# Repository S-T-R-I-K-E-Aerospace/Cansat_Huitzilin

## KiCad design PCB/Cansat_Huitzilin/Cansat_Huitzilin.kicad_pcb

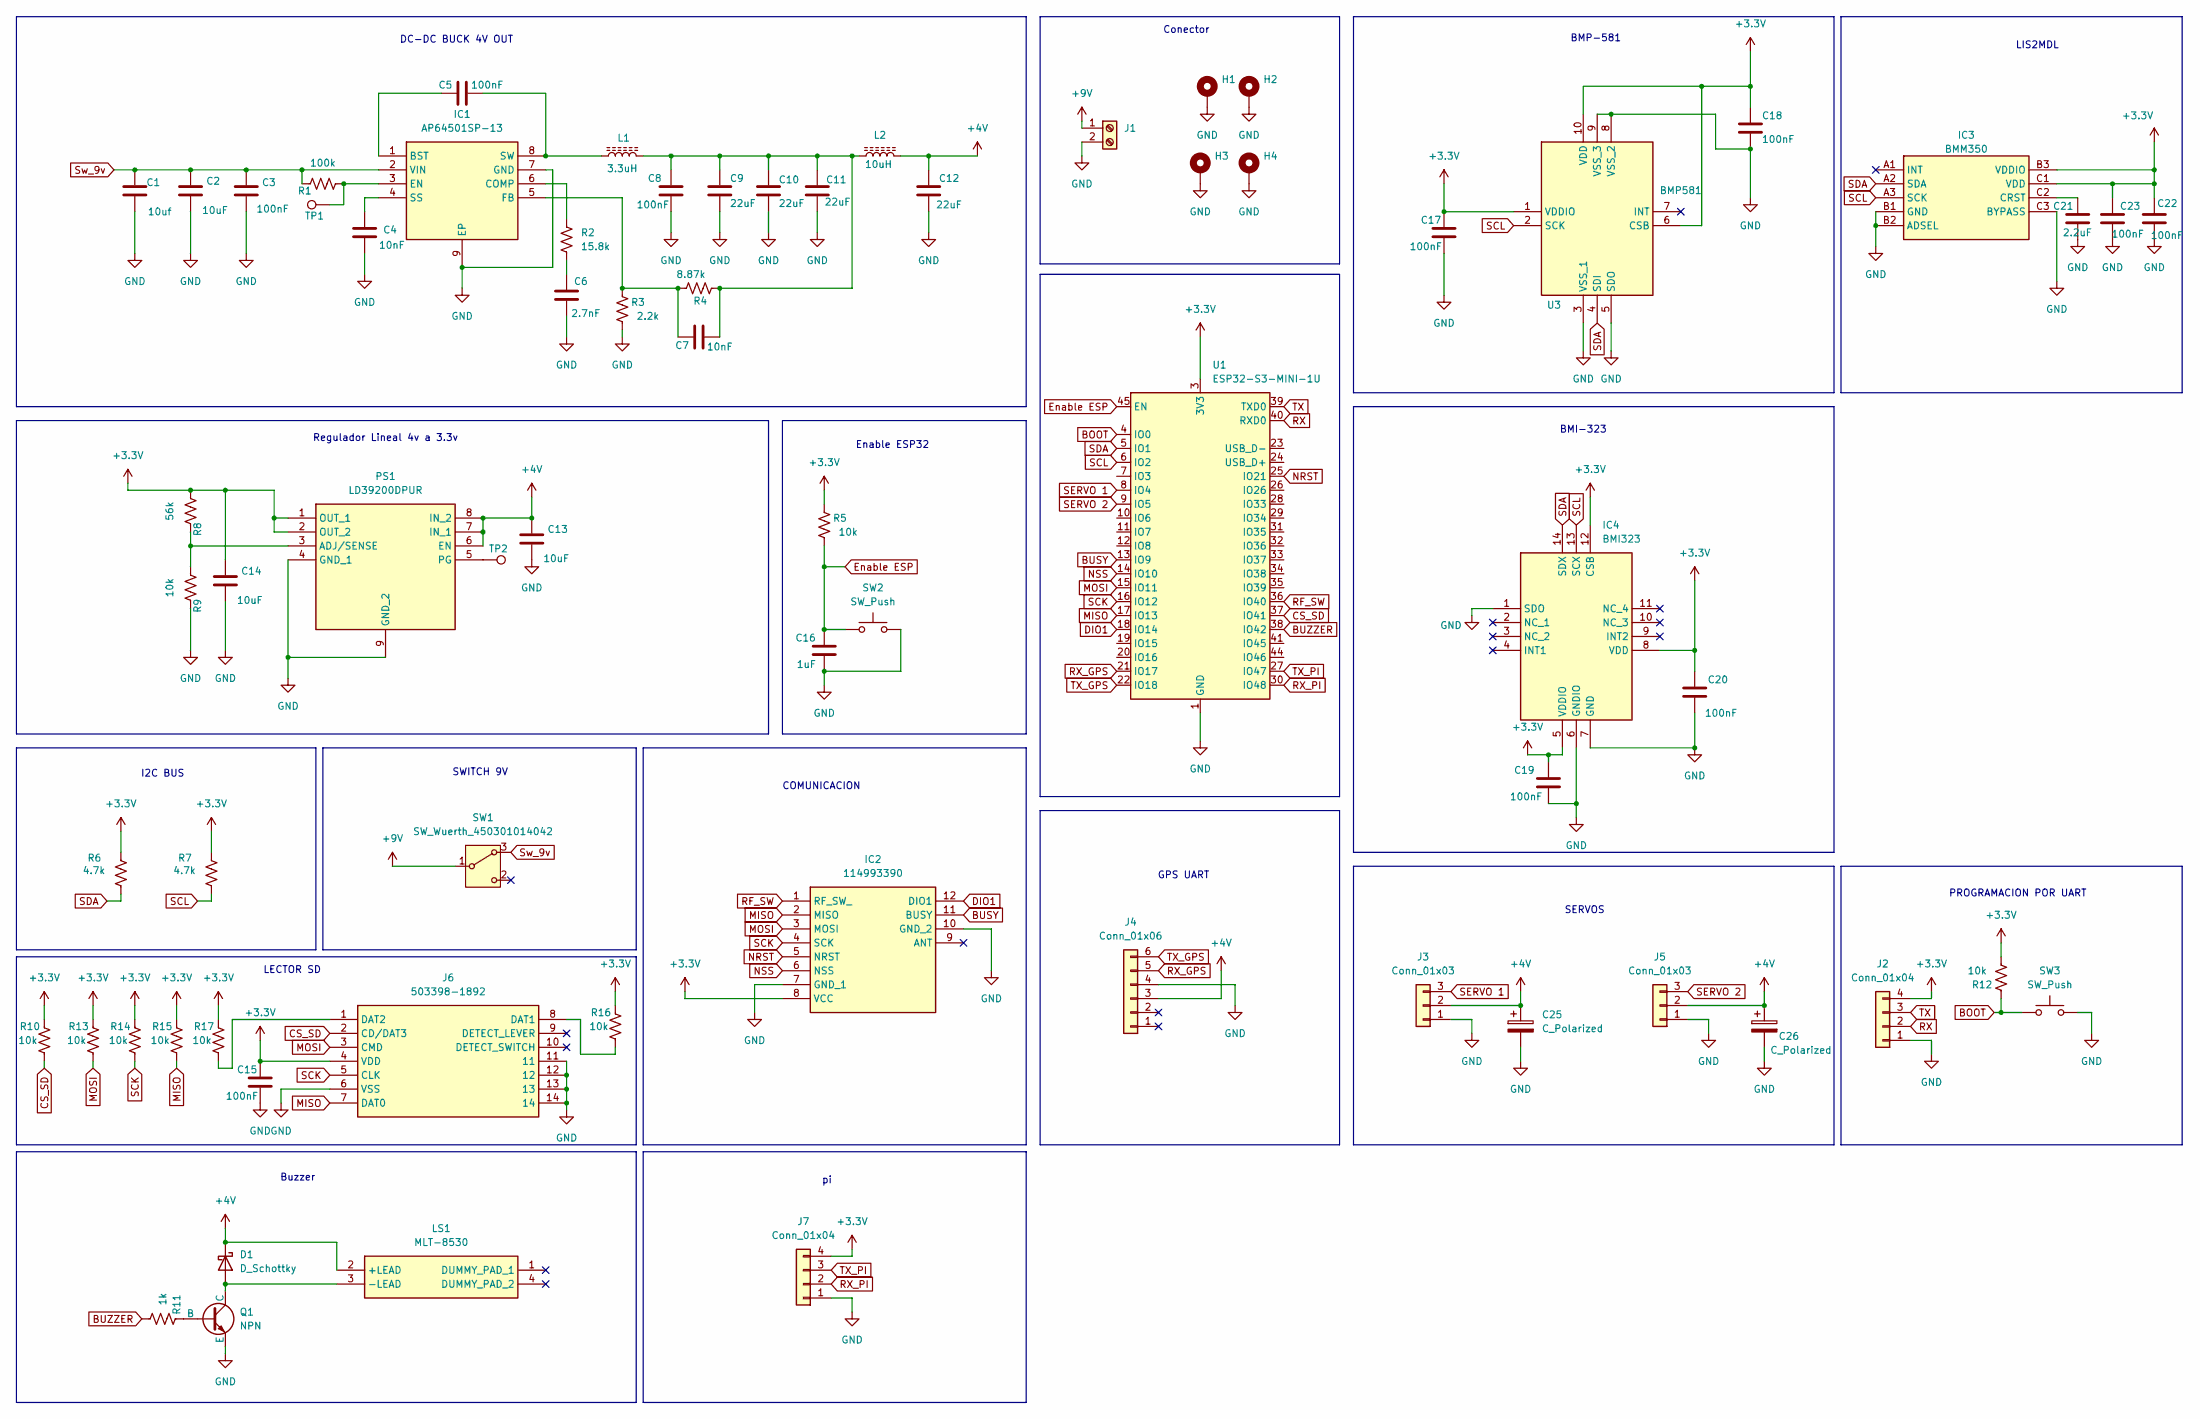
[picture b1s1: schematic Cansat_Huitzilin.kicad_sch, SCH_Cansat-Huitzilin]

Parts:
C1: 10uf; C_0603_1608Metric; Part Number CL10A106MA8NRNC
C2, C13, C14: 10uF; C_0603_1608Metric; Part Number CL10A106MA8NRNC
C3, C5, C8, C15, C17, C18, C19, C20, C22, C23: 100nF; C_0603_1608Metric; Part Number E0603X7R104K500NTD
C4, C7: 10nF; C_0603_1608Metric; Part Number C0201X7R103K500NTA
C6: 2.7nF; C_0603_1608Metric; Part Number C0603C272K5RACTU
C9, C10, C11, C12: 22uF; C_0603_1608Metric
C16: 1uF; C_0603_1608Metric; Part Number CL31B105KBHNNNE
C21: 2.2uF; C_0603_1608Metric; Part Number CL10E224KA84PNC
C25, C26: C_Polarized; CP_Elec_6.3x5.8; Part Number UUD1E101MCL1GS
D1: D_Schottky; D_SOD-123F; Part Number DSS14U
H1, H2, H3, H4: MountingHole_Pad; MountingHole_3.2mm_M3_Pad_Via
IC1: AP64501SP-13; SOIC-8-1EP_3.9x4.9mm_P1.27mm_EP2.29x3mm; Manufacturer_Part_Number AP64501SP-13; Mouser Part Number 621-AP64501SP-13
IC2: 114993390; Mouser Part Number 713-114993390
IC3: BMM350; BGA9C40P3X3_128X128X54; Manufacturer_Part_Number BMM350; Mouser Part Number 262-BMM350
IC4: BMI323; Manufacturer_Part_Number BMI323; Mouser Part Number 262-BMI323
J1: Screw_Terminal_01x02; TerminalBlock_MaiXu_MX126-5.0-02P_1x02_P5.00mm
J2, J7: Conn_01x04; PinHeader_1x04_P2.54mm_Vertical
J3, J5: Conn_01x03; PinHeader_1x03_P2.54mm_Vertical
J4: Conn_01x06; SM06BPASSTBTLFSN
J6: 503398-1892; 5033981892; Manufacturer_Part_Number 503398-1892; Mouser Part Number 538-503398-1892
L1: 3.3uH; L_Wuerth_WE-PD-Typ-LS; Part Number 7447779003
L2: 10uH; L_1210_3225Metric_Pad1.42x2.65mm_HandSolder
LS1: MLT-8530; MLT8530; Manufacturer_Part_Number MLT-8530
PS1: LD39200DPUR; SON80P400X400X100-9N-D; Mouser Part Number 511-LD39200DPUR
Q1: NPN; SOT-23; Part Number S8050
R1: 100k; R_0603_1608Metric; Part Number RC0805FR-07100KL
R2: 15.8k; R_0603_1608Metric; Part Number RMCF0805FT15K8
R3: 2.2k; R_0603_1608Metric; Part Number CRG0805F2K2
R4: 8.87k; R_0603_1608Metric; Part Number RC0805FR-078K87L
R5, R10, R12, R13, R14, R15, R16, R17: 10k; R_0603_1608Metric; Part Number CRCW080510K0FKEA
R6, R7: 4.7k; R_0603_1608Metric; Part Number CRCW08054K70FKEAC
R8: 56k; R_0603_1608Metric; Part Number RC0805FR-07100KL
R9: 10k; R_0603_1608Metric; Part Number RC0805FR-07100KL
R11: 1k; R_0603_1608Metric; Part Number CRCW080510K0FKEA
SW1: SW_Wuerth_450301014042; SW_Slide-03_Wuerth-WS-SLTV_10x2.5x6.4_P2.54mm
SW2, SW3: SW_Push; SW_SPST_SKQG_WithoutStem
TP1, TP2: TestPoint; TestPoint_Pad_D1.0mm
U1: ESP32-S3-MINI-1U; ESP32-S2-MINI-1U
U3: BMP581; Manufacturer_Part_Number BMP581; Mouser Part Number 262-BMP581

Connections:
+3.3V: C14.1, C15.1, C17.1, C18.1, C19.1, C20.1, C22.2, C23.1, IC2.8 (VCC), IC3.B3 (VDDIO), IC3.C1 (VDD), IC4.5 (VDDIO), IC4.8 (VDD), IC4.12 (CSB), J2.4, J6.4 (VDD), J7.4, PS1.1 (OUT_1), PS1.2 (OUT_2), R5.2, R6.1, R7.1, R8.2, R10.2, R12.1, R13.2, R14.2, R15.2, R16.2, R17.2, U1.3 (3V3), U3.1 (VDDIO), U3.6 (CSB), U3.10 (VDD)
+4V: C12.1, C13.1, C25.1, C26.1, D1.1 (K), J3.2, J4.3, J5.2, L2.2, LS1.2 (+LEAD), PS1.6 (EN), PS1.7 (IN_1), PS1.8 (IN_2)
+9V: J1.1, SW1.1 (B)
BOOT: R12.2, SW3.1, U1.4 (IO0)
BUSY: IC2.11 (BUSY), U1.13 (IO9)
BUZZER: R11.1, U1.38 (IO42)
CS_SD: J6.2 (CD/DAT3), R10.1, U1.37 (IO41)
DIO1: IC2.12 (DIO1), U1.18 (IO14)
Enable ESP: C16.1, R5.1, SW2.1, U1.45 (EN)
GND: C1.2, C2.2, C3.2, C4.2, C6.2, C8.2, C9.2, C10.2, C11.2, C12.2, C13.2, C14.2, C15.2, C16.2, C17.2, C18.2, C19.2, C20.2, C21.2, C22.1, C23.2, C25.2, C26.2, H1.1, H2.1, H3.1, H4.1, IC1.7 (GND), IC1.9 (EP), IC2.7 (GND_1), IC2.10 (GND_2), IC3.B1 (GND), IC3.B2 (ADSEL), IC3.C3 (BYPASS), IC4.1 (SDO), IC4.6 (GNDIO), IC4.7 (GND), J1.2, J2.1, J3.1, J4.4, J5.1, J6.6 (VSS), J6.11, J6.12, J6.13, J6.14, J7.1, PS1.4 (GND_1), PS1.9 (GND_2), Q1.3 (E), R3.1, R9.1, SW2.2, SW3.2, U1.1 (GND), U1.2 (GND), U1.42 (GND), U1.43 (GND), U1.46 (GND), U1.47 (GND), U1.48 (GND), U1.49 (GND), U1.50 (GND), U1.51 (GND), U1.52 (GND), U1.53 (GND), U1.54 (GND), U1.55 (GND), U1.56 (GND), U1.57 (GND), U1.58 (GND), U1.59 (GND), U1.60 (GND), U1.61 (GND), U1.62 (GND), U1.63 (GND), U1.64 (GND), U1.65 (GND), U3.3 (VSS_1), U3.5 (SDO), U3.8 (VSS_2), U3.9 (VSS_3)
MISO: IC2.2 (MISO), J6.7 (DAT0), R15.1, U1.17 (IO13)
MOSI: IC2.3 (MOSI), J6.3 (CMD), R13.1, U1.15 (IO11)
NRST: IC2.5 (NRST), U1.25 (IO21)
NSS: IC2.6 (NSS), U1.14 (IO10)
unnamed: C6.1, R2.1
unnamed: C7.2, C8.1, C9.1, C10.1, C11.1, L1.2, L2.1, R4.1
unnamed: D1.2 (A), LS1.3 (-LEAD), Q1.1 (C)
unnamed: C5.1, IC1.1 (BST)
unnamed: IC1.6 (COMP), R2.2
unnamed: IC1.3 (EN), R1.2, TP1.1
unnamed: C7.1, IC1.5 (FB), R3.2, R4.2
unnamed: C4.1, IC1.4 (SS)
unnamed: C5.2, IC1.8 (SW), L1.1
unnamed: C21.1, IC3.C2 (CRST)
unnamed: J6.8 (DAT1), R16.1
unnamed: J6.1 (DAT2), R17.1
unnamed: PS1.3 (ADJ/SENSE), R8.1, R9.2
unnamed: PS1.5 (PG), TP2.1
unnamed: Q1.2 (B), R11.2
RF_SW: IC2.1 (RF_SW_), U1.36 (IO40)
RX: J2.2, U1.40 (RXD0)
RX_GPS: J4.5, U1.21 (IO17)
RX_PI: J7.2, U1.30 (IO48)
SCK: IC2.4 (SCK), J6.5 (CLK), R14.1, U1.16 (IO12)
SCL: IC3.A3 (SCK), IC4.13 (SCX), R7.2, U1.6 (IO2), U3.2 (SCK)
SDA: IC3.A2 (SDA), IC4.14 (SDX), R6.2, U1.5 (IO1), U3.4 (SDI)
SERVO 1: J3.3, U1.8 (IO4)
SERVO 2: J5.3, U1.9 (IO5)
Sw_9v: C1.1, C2.1, C3.1, IC1.2 (VIN), R1.1, SW1.3 (A)
TX: J2.3, U1.39 (TXD0)
TX_GPS: J4.6, U1.22 (IO18)
TX_PI: J7.3, U1.27 (IO47)

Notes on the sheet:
LECTOR SD
BMI-323
PROGRAMACION POR UART
I2C BUS
GPS UART
Regulador Lineal 4v a 3.3v
BMP-581
SWITCH 9V
DC-DC BUCK 4V OUT
LIS2MDL
COMUNICACION
Conector
Buzzer
Enable ESP32
SERVOS

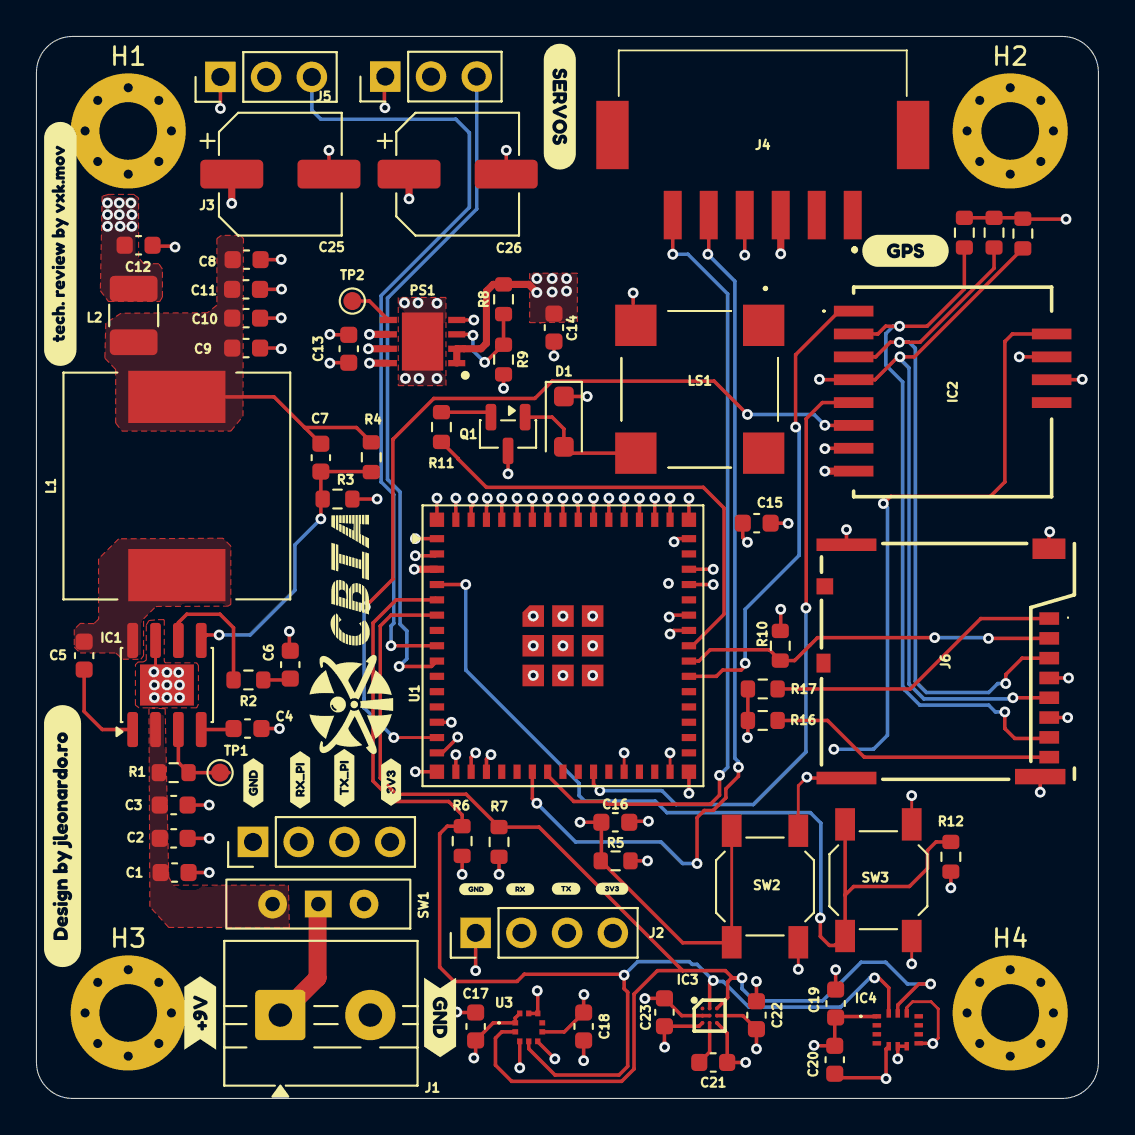
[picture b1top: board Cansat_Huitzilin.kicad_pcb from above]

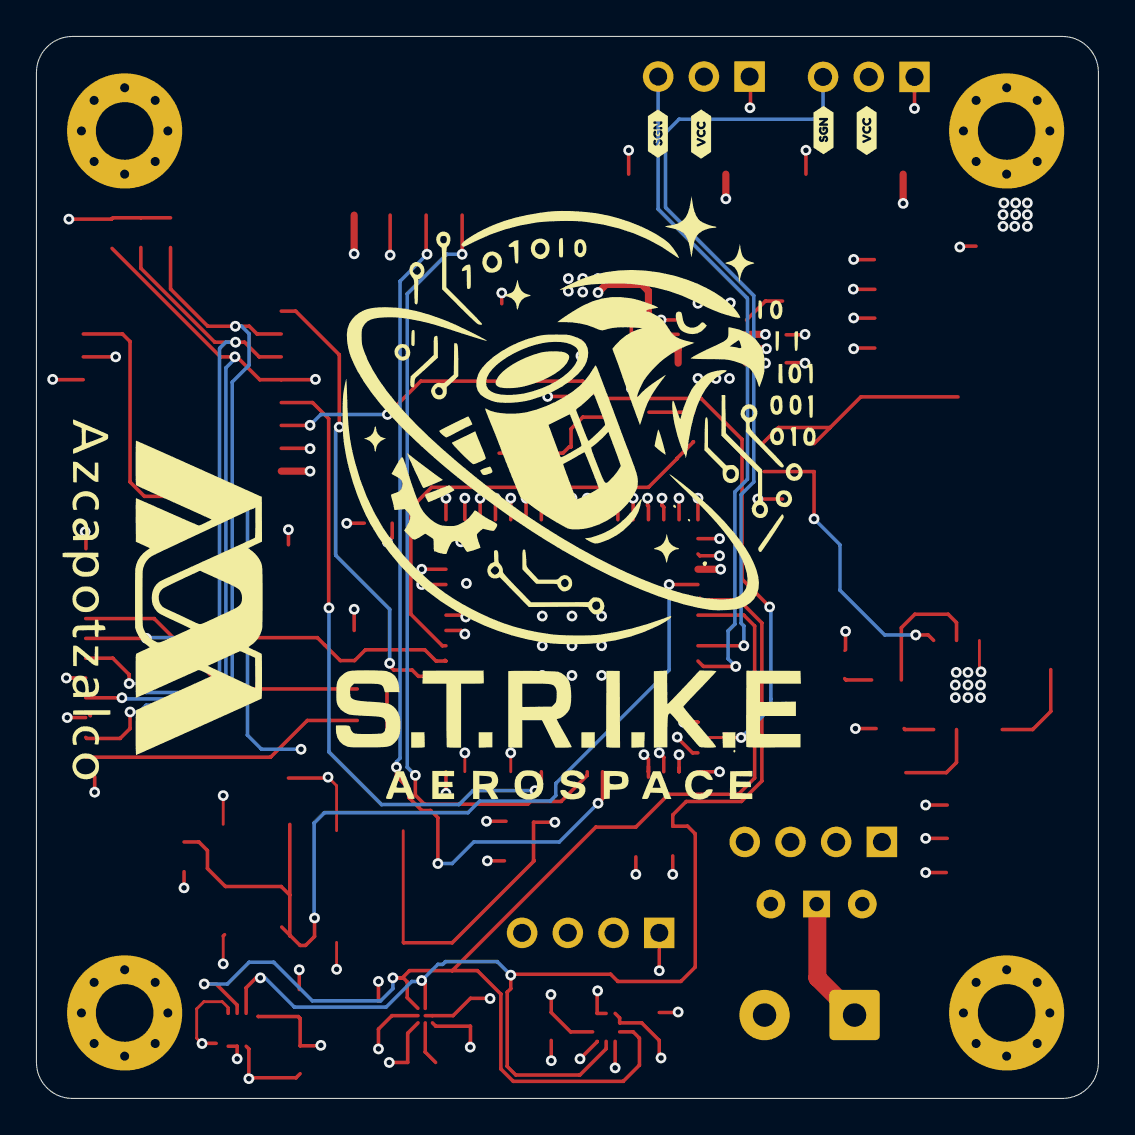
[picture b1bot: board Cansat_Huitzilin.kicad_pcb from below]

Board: 4 copper layers, 59.0 x 59.0 mm, 88 parts (4 on the bottom side), 42 nets.

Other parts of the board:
kibuzzard-69ACDBDC: G***; kibuzzard-69ACDBDC
kibuzzard-69ACDC11: G***; kibuzzard-69ACDC11
kibuzzard-69ACDC24: G***; kibuzzard-69ACDC24
kibuzzard-69ACDC57: G***; kibuzzard-69ACDC57
kibuzzard-69ACDEB2, kibuzzard-69ACDEB2#2: G***; kibuzzard-69ACDEB2
kibuzzard-69ACDECD, kibuzzard-69ACDECD#2: G***; kibuzzard-69ACDECD
kibuzzard-69ADC2FE: G***; kibuzzard-69ADC2FE
kibuzzard-69ADC3B5: G***; kibuzzard-69ADC3B5
kibuzzard-69ADC4A7: G***; kibuzzard-69ADC4A7
kibuzzard-69ADC45A: G***; kibuzzard-69ADC45A
kibuzzard-69ADC49F: G***; kibuzzard-69ADC49F
kibuzzard-69ADC375: G***; kibuzzard-69ADC375
kibuzzard-69ADC389: G***; kibuzzard-69ADC389
kibuzzard-69ADC495: G***; kibuzzard-69ADC495
kibuzzard-69CE0A89: G***; kibuzzard-69CE0A89
kibuzzard-69CE31E7: G***; kibuzzard-69CE31E7

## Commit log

2025-10-29 folders
2025-10-29 create kicadprj and add 3dmodels
2025-11-10 start??
2025-11-10 start new design
2025-11-12 prueba en g312
2025-11-12 deshaciendo cambios
2025-11-12 aero
    define the new dimensions of NACA profiles
2025-11-14 more or less
    i finished the naca profiles and the support of the profiles and start a enclousure for de deployment system
2025-11-16 finish 3d model
    finish the 3d modelling and the 3d assembly
2025-11-21 add 3d printable models
2025-12-01 little changes
2025-12-09 make another files
2025-12-09 save changes
2025-12-09 Add CERN Open Hardware Licence
    Added CERN Open Hardware Licence Version 2 - Strongly Reciprocal to the project.
2025-12-09 Delete objets
    delete files
    delete files for a pull request
2025-12-09 Merge: Recuperando archivos de diseño desde feature/nuevasPiezas
2025-12-09 Cambios en Liberacion
    Cambios la sujeccion, se cambiaron las dimensiones de los tornillos, junto con un mejor ensamble.
2025-12-09 Modificaciones a Huevo
    Se hizo un empalme en toda la esctructura exterior
2026-01-20 Autogiro
    Se rediseñaron las piezas del sistema de autogiro ajustandolas a nuevas formas de sujetar las secciones.
2026-01-20 Archivos
    limpieza de archivos
2026-01-20 Prepare for merge
    Preparacion de archivos binarios para merge posterior
2026-01-20 prepare for merge
2026-02-13 Actualización de la PCB
2026-02-14 Actualización del diseño PCB
2026-03-07 PCB-m
2026-03-07 PCB
    Modify the track spacing
2026-03-07 PCB actualizado desde el esquemático
2026-03-08 PCB
    adding the final serigraphy
2026-03-08 Modelo 3D
2026-03-08 Agregando librerias al proyecto
2026-03-08 Librerias
2026-03-10 GUI & PCB
    Complete Mission Control v1.0.1 and integrate final CanSat PCB + libraries
2026-03-10 modifying the gitignore
2026-04-22 save
